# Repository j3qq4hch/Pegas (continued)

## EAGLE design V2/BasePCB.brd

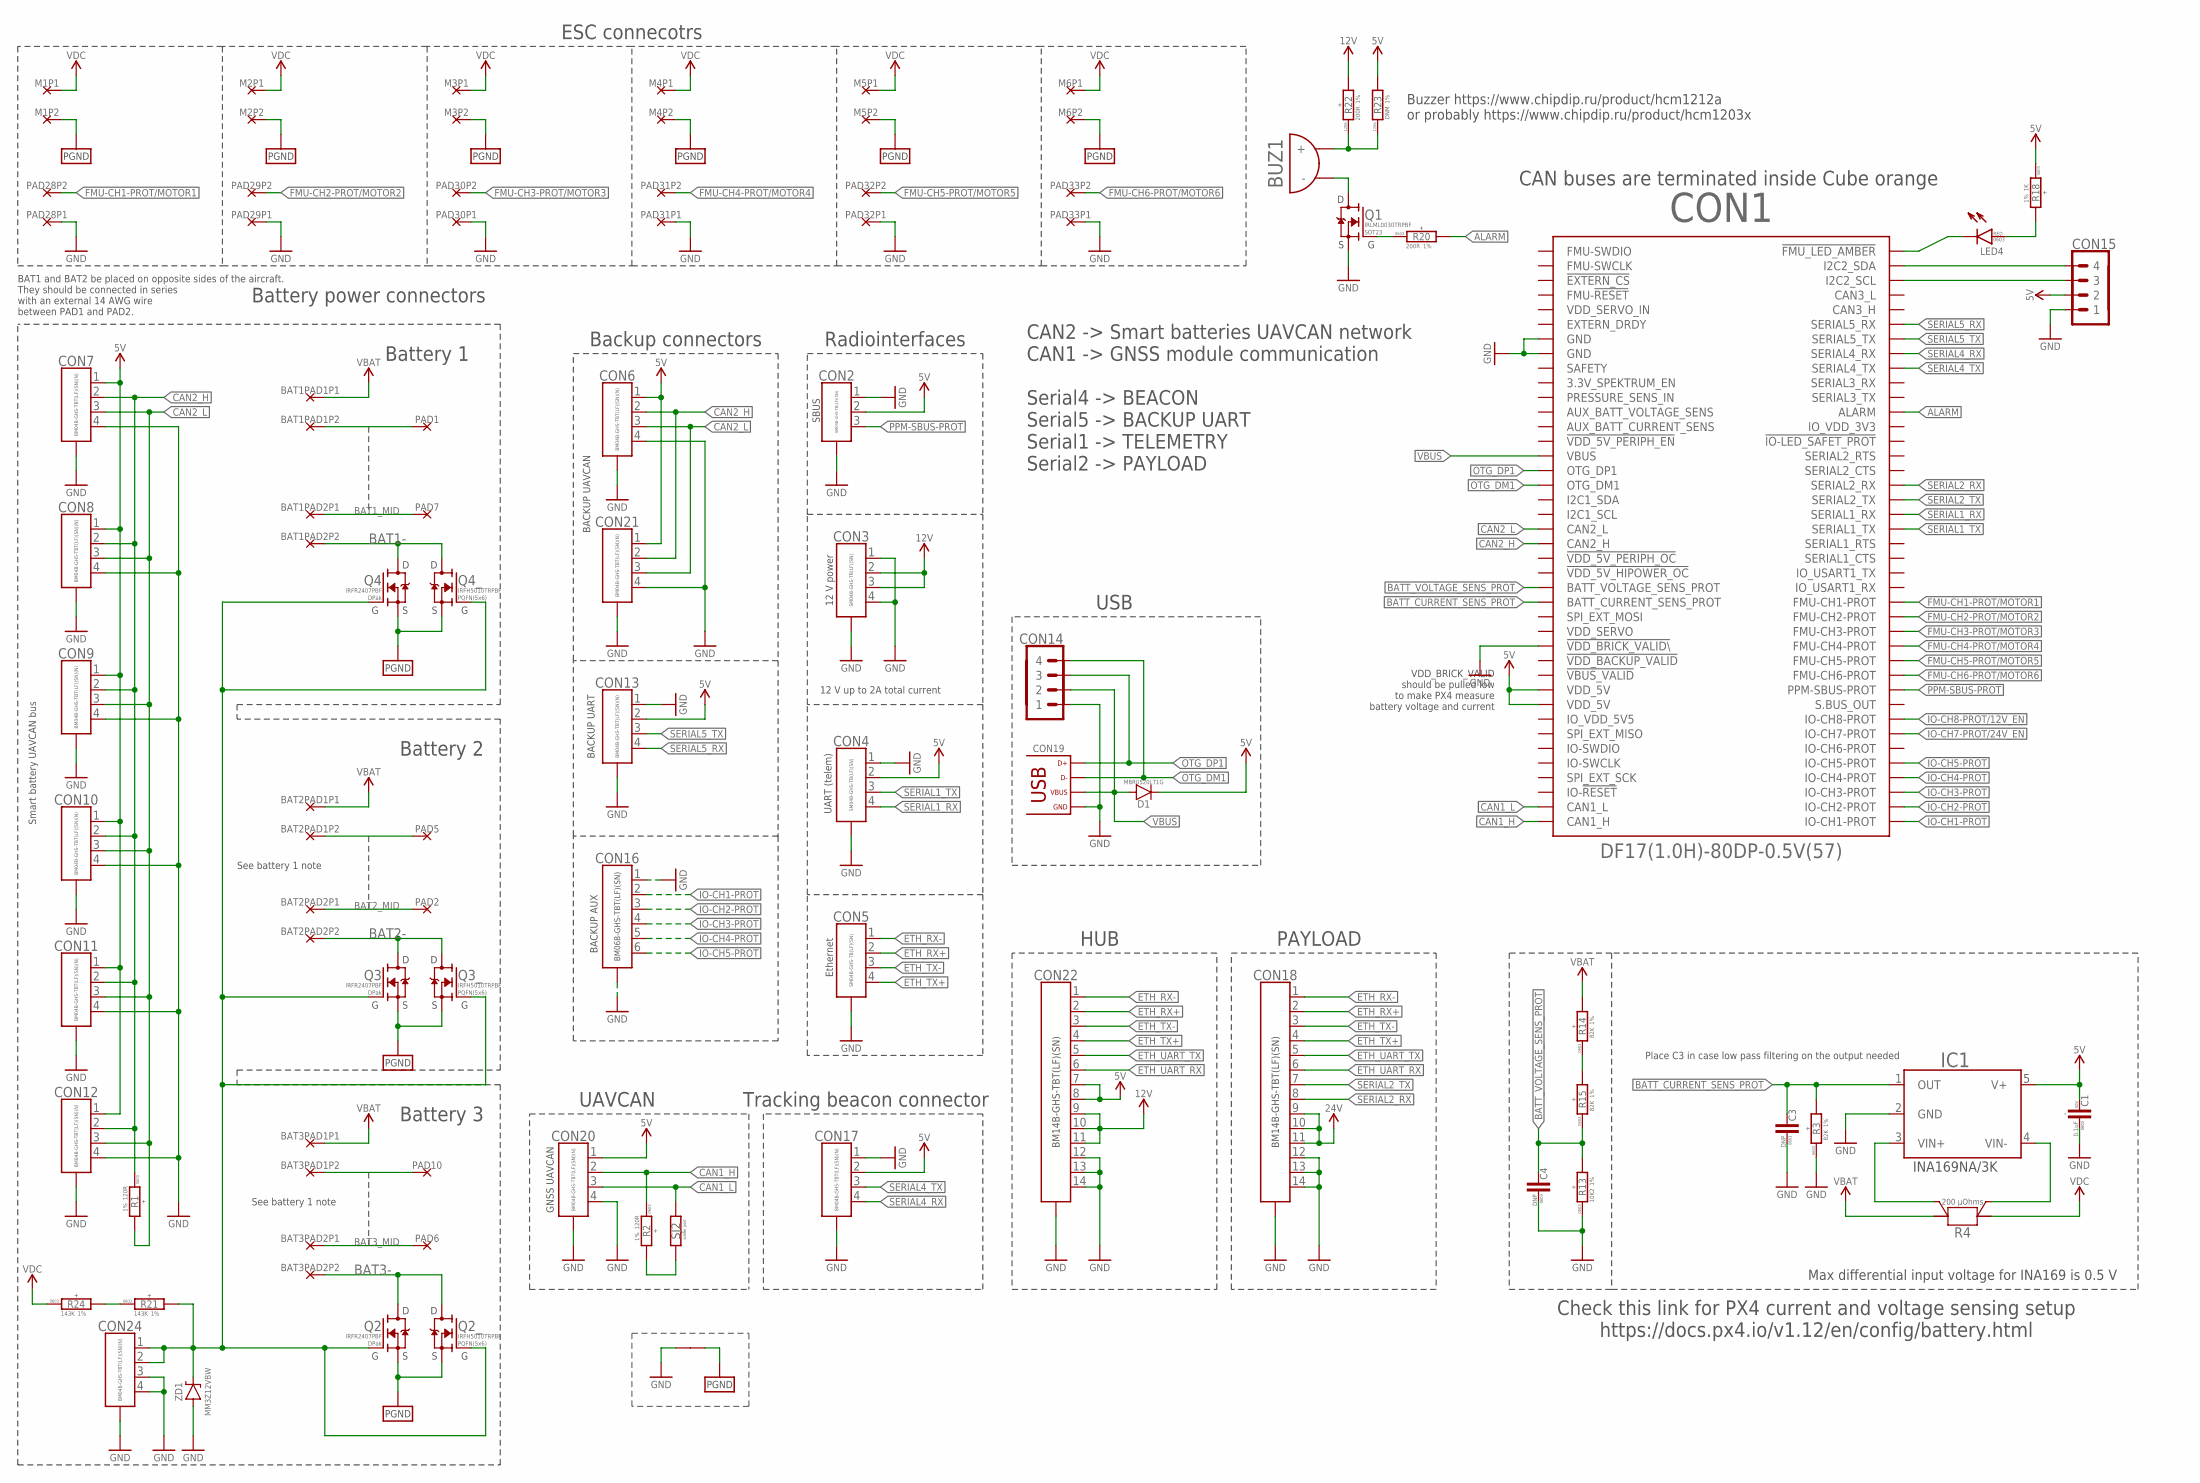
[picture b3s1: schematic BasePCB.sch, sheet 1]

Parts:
BAT1PAD1, BAT1PAD2, BAT2PAD1, BAT2PAD2, BAT3PAD1, BAT3PAD2: PAD_PAIR-4X10; 4X10_PAIR
BUZ1: BUZZER-ЕР-12MM; BUZZER_12MM
C1: 0.1uF; C0603; VOLTAGE 50V; LCSC# C14663
C3, C4: DNP; C0603
CON1: CUBE_ORANGE_; CUBE_ORANGE
CON2: CON-3P-TABS-JST-GH-SIDE; SM03B-GHS-TB
CON3, CON4, CON5: CON-4P-TABS-JST-GH-SIDE; SM04B-GHS-TB
CON6, CON7, CON8, CON9, CON10, CON11, CON12, CON13, CON17, CON20, CON21, CON24: CON-4P-TABS-JST-GH-TOP; BM04B-GHS-TB
CON14, CON15: PINHEAD_1X04-2.54; 1X04-PTH-2.54
CON16: CON-6P-TABS-JST-GH-TOP; BM06B-GHS-TBT
CON18, CON22: CON-14P-TABS-JST-GH-TOP; BM14B-GHS-TBT
CON19: USB-TYPE-C-VERT-PROD; 2047110001-PROD; LCSC# C381139
D1: MBR0520L-SOD123; SOD123
IC1: INA169; SOT23-5
J1: CONNECTION-SMD-BIG; CONNECTION_BIG
LED4: LED-0603; LED0603; LCSC# C2286
M1, M2, M3, M4, M5, M6: PAD_PAIR-4X10; 4X10_PAIR
PAD1, PAD2, PAD5, PAD6, PAD7, PAD10: PAD-10X4; 10X4
PAD28, PAD29, PAD30, PAD31, PAD32, PAD33: PAD_PAIR-2X6; 2X6_PAIR
Q1: IRLML0030; SOT23
Q2, Q3, Q4: IRFR2407PBF; D-PAK
Q2_, Q3_, Q4_: IRFH5010TRPBF-DFN5X6; PG-TDSON-8
R1, R2: 120R; R0603; LCSC# C22787
R3, R14, R15: 82K; R0603; LCSC# C23254
R4: 200 µOhms; R3920-KELVIN
R13: 10K2; R0603; LCSC# C22772
R18: 1K; R0603; LCSC# C21190
R20: 200R; R0603; LCSC# C21190
R21, R24: 143K; R0603; LCSC# C22877
R22: 200R; R1206; LCSC# C25361
R23: DNM; R1206
SJ2: SOLDER_JOINT-SJ1; RES_0
ZD1: MM3Z12VBW; SOD323

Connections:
!FMU_LED_AMBER: CON1.2 (!FMU_LED_AMBER), LED4.C
ALARM: CON1.24 (ALARM), R20.2
BAT1-: BAT1PAD2.2, Q4.D, Q4_.5D (D), Q4_.6D (D), Q4_.7D (D), Q4_.8D (D), Q4_.PAD_D (D)
BAT1_MID: BAT1PAD2.1, PAD7.P$1
BAT2-: BAT2PAD2.2, Q3.D, Q3_.5D (D), Q3_.6D (D), Q3_.7D (D), Q3_.8D (D), Q3_.PAD_D (D)
BAT2_MID: BAT2PAD2.1, PAD2.P$1
BAT3-: BAT3PAD2.2, Q2.D, Q2_.5D (D), Q2_.6D (D), Q2_.7D (D), Q2_.8D (D), Q2_.PAD_D (D)
BAT3_MID: BAT3PAD2.1, PAD6.P$1
BATT_CURRENT_SENS_PROT: C3.2, CON1.49 (BATT_CURRENT_SENS_PROT), IC1.1 (OUT), R3.2
BATT_VOLTAGE_SENS_PROT: C4.2, CON1.47 (BATT_VOLTAGE_SENS_PROT), R13.2, R15.1
CAN1_H: CON1.79 (CAN1_H), CON20.2, R2.1
CAN1_L: CON1.77 (CAN1_L), CON20.3, SJ2.2
CAN2_H: CON1.41 (CAN2_H), CON6.2, CON7.2, CON8.2, CON9.2, CON10.2, CON11.2, CON12.2, CON21.2, R1.1
CAN2_L: CON1.39 (CAN2_L), CON6.3, CON7.3, CON8.3, CON9.3, CON10.3, CON11.3, CON12.3, CON21.3, R1.2
ETH_RX+: CON5.2, CON18.2, CON22.2
ETH_RX-: CON5.1, CON18.1, CON22.1
ETH_TX+: CON5.4, CON18.4, CON22.4
ETH_TX-: CON5.3, CON18.3, CON22.3
ETH_UART_RX: CON18.6, CON22.6
ETH_UART_TX: CON18.5, CON22.5
FMU-CH1-PROT/MOTOR1: CON1.50 (FMU-CH1-PROT), PAD28.2
FMU-CH2-PROT/MOTOR2: CON1.52 (FMU-CH2-PROT), PAD29.2
FMU-CH3-PROT/MOTOR3: CON1.54 (FMU-CH3-PROT), PAD30.2
FMU-CH4-PROT/MOTOR4: CON1.56 (FMU-CH4-PROT), PAD31.2
FMU-CH5-PROT/MOTOR5: CON1.58 (FMU-CH5-PROT), PAD32.2
FMU-CH6-PROT/MOTOR6: CON1.60 (FMU-CH6-PROT), PAD33.2
GND: C1.1, C3.1, C4.1, CON1.13 (GND), CON1.15 (GND), CON1.55 (!VDD_BRICK_VALID\), CON2.1, CON2.M$0 (GND), CON2.M$1 (GND), CON3.1, CON3.4, CON3.M$0 (GND), CON3.M$1 (GND), CON4.1, CON4.M$0 (GND), CON4.M$1 (GND), CON5.M$0 (GND), CON5.M$1 (GND), CON6.4, CON6.M$0 (GND), CON6.M$1 (GND), CON7.4, CON7.M$0 (GND), CON7.M$1 (GND), CON8.4, CON8.M$0 (GND), CON8.M$1 (GND), CON9.4, CON9.M$0 (GND), CON9.M$1 (GND), CON10.4, CON10.M$0 (GND), CON10.M$1 (GND), CON11.4, CON11.M$0 (GND), CON11.M$1 (GND), CON12.4, CON12.M$0 (GND), CON12.M$1 (GND), CON13.1, CON13.M$0 (GND), CON13.M$1 (GND), CON14.1, CON15.1, CON16.1, CON16.M$0 (G1), CON16.M$1 (G1), CON17.1, CON17.M$0 (GND), CON17.M$1 (GND), CON18.12, CON18.13, CON18.14, CON18.M$0 (G1), CON18.M$1 (G1), CON19.A1 (GND), CON19.A12 (GND), CON19.B1 (GND), CON19.B12 (GND), CON19.G1 (GND), CON19.G2 (GND), CON19.G4 (GND), CON19.G5 (GND), CON19.G7 (GND), CON19.G8 (GND), CON19.G9 (GND), CON19.G10 (GND), CON19.P$1 (GND), CON19.P$2 (GND), CON20.4, CON20.M$0 (GND), CON20.M$1 (GND), CON21.4, CON21.M$0 (GND), CON21.M$1 (GND), CON22.12, CON22.13, CON22.14, CON22.M$0 (G1), CON22.M$1 (G1), CON24.3, CON24.4, CON24.M$0 (GND), CON24.M$1 (GND), IC1.2 (GND), J1.1, PAD28.1, PAD29.1, PAD30.1, PAD31.1, PAD32.1, PAD33.1, Q1.2 (S), R3.1, R13.1, ZD1.A; also elsewhere on the board
I2C2_SCL: CON1.6 (I2C2_SCL), CON15.3
I2C2_SDA: CON1.4 (I2C2_SDA), CON15.4
IO-CH1-PROT: CON1.80 (IO-CH1-PROT), CON16.2
IO-CH2-PROT: CON1.78 (IO-CH2-PROT), CON16.3
IO-CH3-PROT: CON1.76 (IO-CH3-PROT), CON16.4
IO-CH4-PROT: CON1.74 (IO-CH4-PROT), CON16.5
IO-CH5-PROT: CON1.72 (IO-CH5-PROT), CON16.6
IO-CH7-PROT/24V_EN: CON1.68 (IO-CH7-PROT); also elsewhere on the board
IO-CH8-PROT/12V_EN: CON1.66 (IO-CH8-PROT); also elsewhere on the board
unnamed: LED4.A, R18.2
unnamed: BAT1PAD1.2, PAD1.P$1
unnamed: BUZ1.2 (-), Q1.3 (D)
unnamed: BAT2PAD1.2, PAD5.P$1
unnamed: Q1.1 (G), R20.1
unnamed: BAT3PAD1.2, PAD10.P$1
unnamed: R2.2, SJ2.1
unnamed: IC1.4 (VIN-), R4.S2
unnamed: IC1.3 (VIN+), R4.S1
unnamed: R14.1, R15.2
unnamed: BUZ1.1 (+), R22.P$1 (1), R23.P$1 (1)
unnamed: R21.1, R24.2
OTG_DM1: CON1.33 (OTG_DM1), CON14.4, CON19.A7 (D-), CON19.B7 (D-)
OTG_DP1: CON1.31 (OTG_DP1), CON14.3, CON19.A6 (D+), CON19.B6 (D+)
PGND: J1.2, M1.2, M2.2, M3.2, M4.2, M5.2, M6.2, Q2.S, Q2_.1S (S), Q2_.2S (S), Q2_.3S (S), Q3.S, Q3_.1S (S), Q3_.2S (S), Q3_.3S (S), Q4.S, Q4_.1S (S), Q4_.2S (S), Q4_.3S (S)
PPM-SBUS-PROT: CON1.62 (PPM-SBUS-PROT), CON2.3
PWR_GATE: CON24.1, CON24.2, Q2.G, Q2_.4G (G), Q3.G, Q3_.4G (G), Q4.G, Q4_.4G (G), R21.2, ZD1.C
SERIAL1_RX: CON1.38 (SERIAL1_RX), CON4.4
SERIAL1_TX: CON1.40 (SERIAL1_TX), CON4.3
SERIAL2_RX: CON1.34 (SERIAL2_RX), CON18.8
SERIAL2_TX: CON1.36 (SERIAL2_TX), CON18.7
SERIAL4_RX: CON1.16 (SERIAL4_RX), CON17.4
SERIAL4_TX: CON1.18 (SERIAL4_TX), CON17.3
SERIAL5_RX: CON1.12 (SERIAL5_RX), CON13.4
SERIAL5_TX: CON1.14 (SERIAL5_TX), CON13.3
VBAT: BAT1PAD1.1, BAT2PAD1.1, BAT3PAD1.1, R4.1, R4.11 (1), R14.2
VBUS: CON1.29 (VBUS), CON14.2, CON19.A4 (VBUS), CON19.B4 (VBUS), D1.A
VDC: M1.1, M2.1, M3.1, M4.1, M5.1, M6.1, R4.2, R4.22 (2), R24.1; also elsewhere on the board
VDD_5V: C1.2, CON1.61 (VDD_5V), CON1.63 (VDD_5V), CON2.2, CON4.2, CON6.1, CON7.1, CON8.1, CON9.1, CON10.1, CON11.1, CON12.1, CON13.2, CON15.2, CON17.2, CON20.1, CON21.1, CON22.7, CON22.8, D1.C, IC1.5 (V+), R18.1, R23.P$2 (2); also elsewhere on the board
VDD_12V: CON3.2, CON3.3, CON22.9, CON22.10, CON22.11, R22.P$2 (2); also elsewhere on the board
VDD_24V: CON18.9, CON18.10, CON18.11; also elsewhere on the board

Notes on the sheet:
SBUS
12 V up to 2A total current
12 V power
UART (telem)
Ethernet
Radiointerfaces
GNSS UAVCAN
Smart battery UAVCAN bus
UAVCAN
BACKUP UAVCAN
Backup connectors
BACKUP UART
BACKUP AUX
Tracking beacon connector
Battery power connectors
ESC connecotrs
BAT1 and BAT2 be placed on opposite sides of the aircraft. They should be connected in series with an external 14 AWG wire between PAD1 and PAD2.
Battery 1
Battery 2
See battery 1 note
Battery 3
CAN buses are terminated inside Cube orange
CAN2 -> Smart batteries UAVCAN network CAN1 -> GNSS module communication Serial4 -> BEACON Serial5 -> BACKUP UART Serial1 -> TELEMETRY Serial2 -> PAYLOAD
Check this link for PX4 current and voltage sensing setup https://docs.px4.io/v1.12/en/config/battery.html
Max differential input voltage for INA169 is 0.5 V
Place C3 in case low pass filtering on the output needed
PAYLOAD
USB
VDD_BRICK_VALID should be pulled low to make PX4 measure battery voltage and current
HUB
Buzzer https://www.chipdip.ru/product/hcm1212a or probably https://www.chipdip.ru/product/hcm1203x

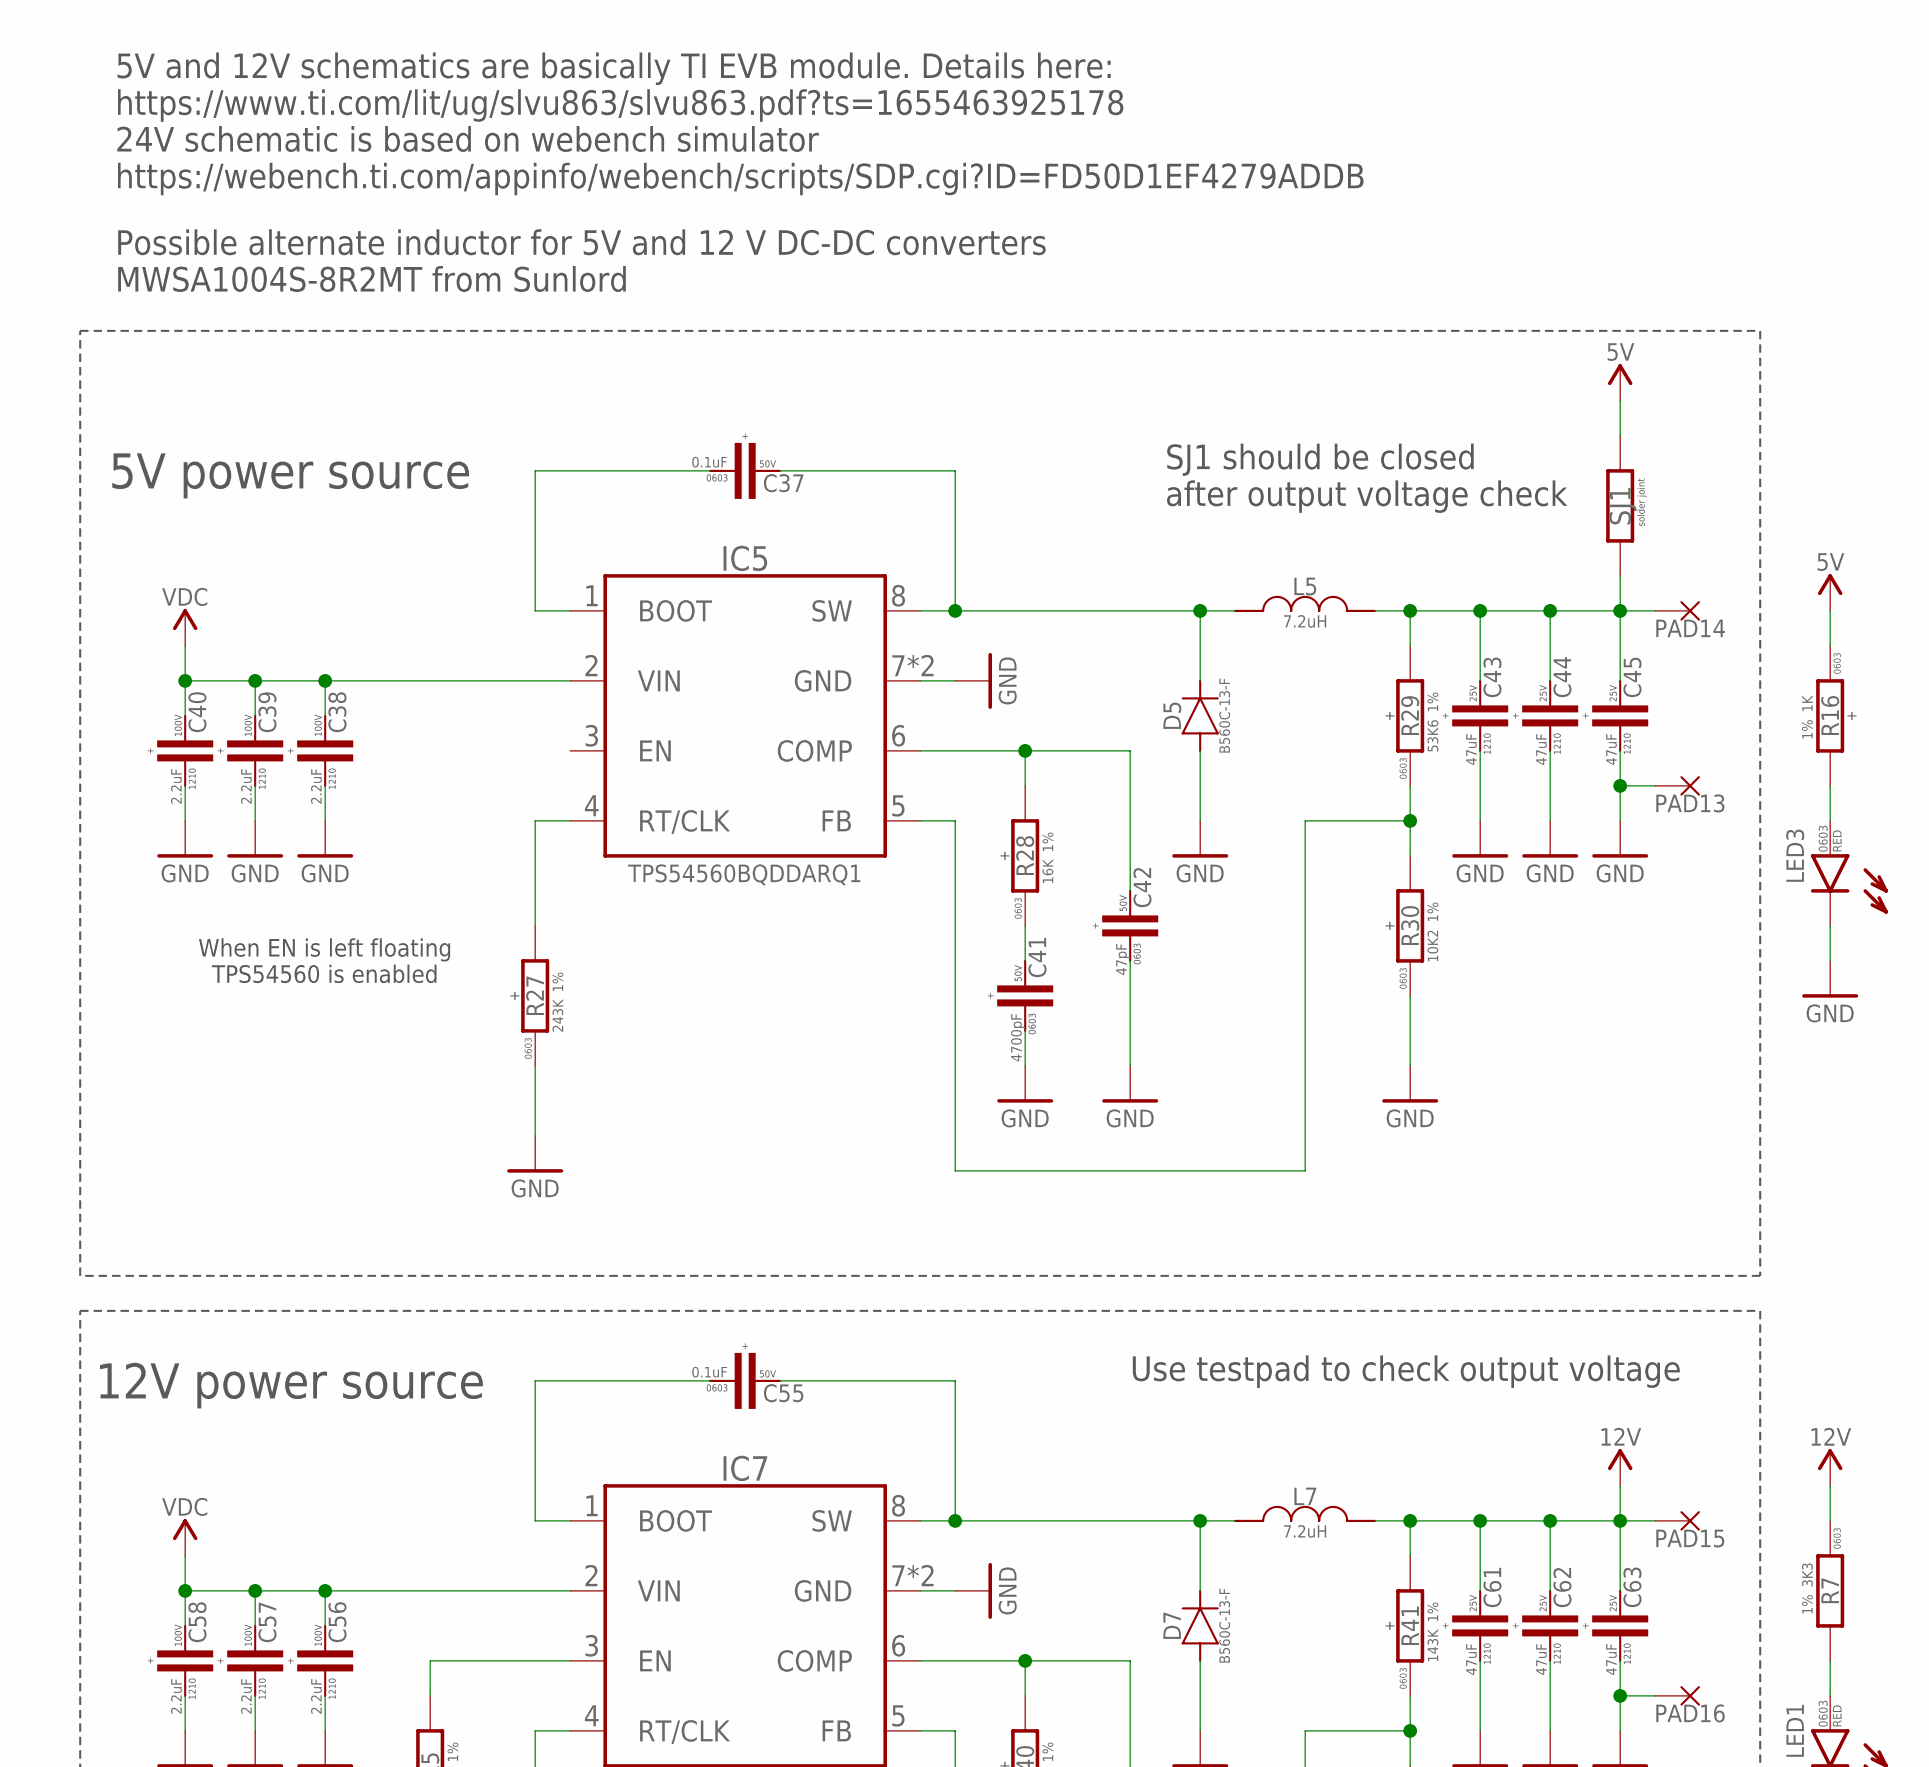
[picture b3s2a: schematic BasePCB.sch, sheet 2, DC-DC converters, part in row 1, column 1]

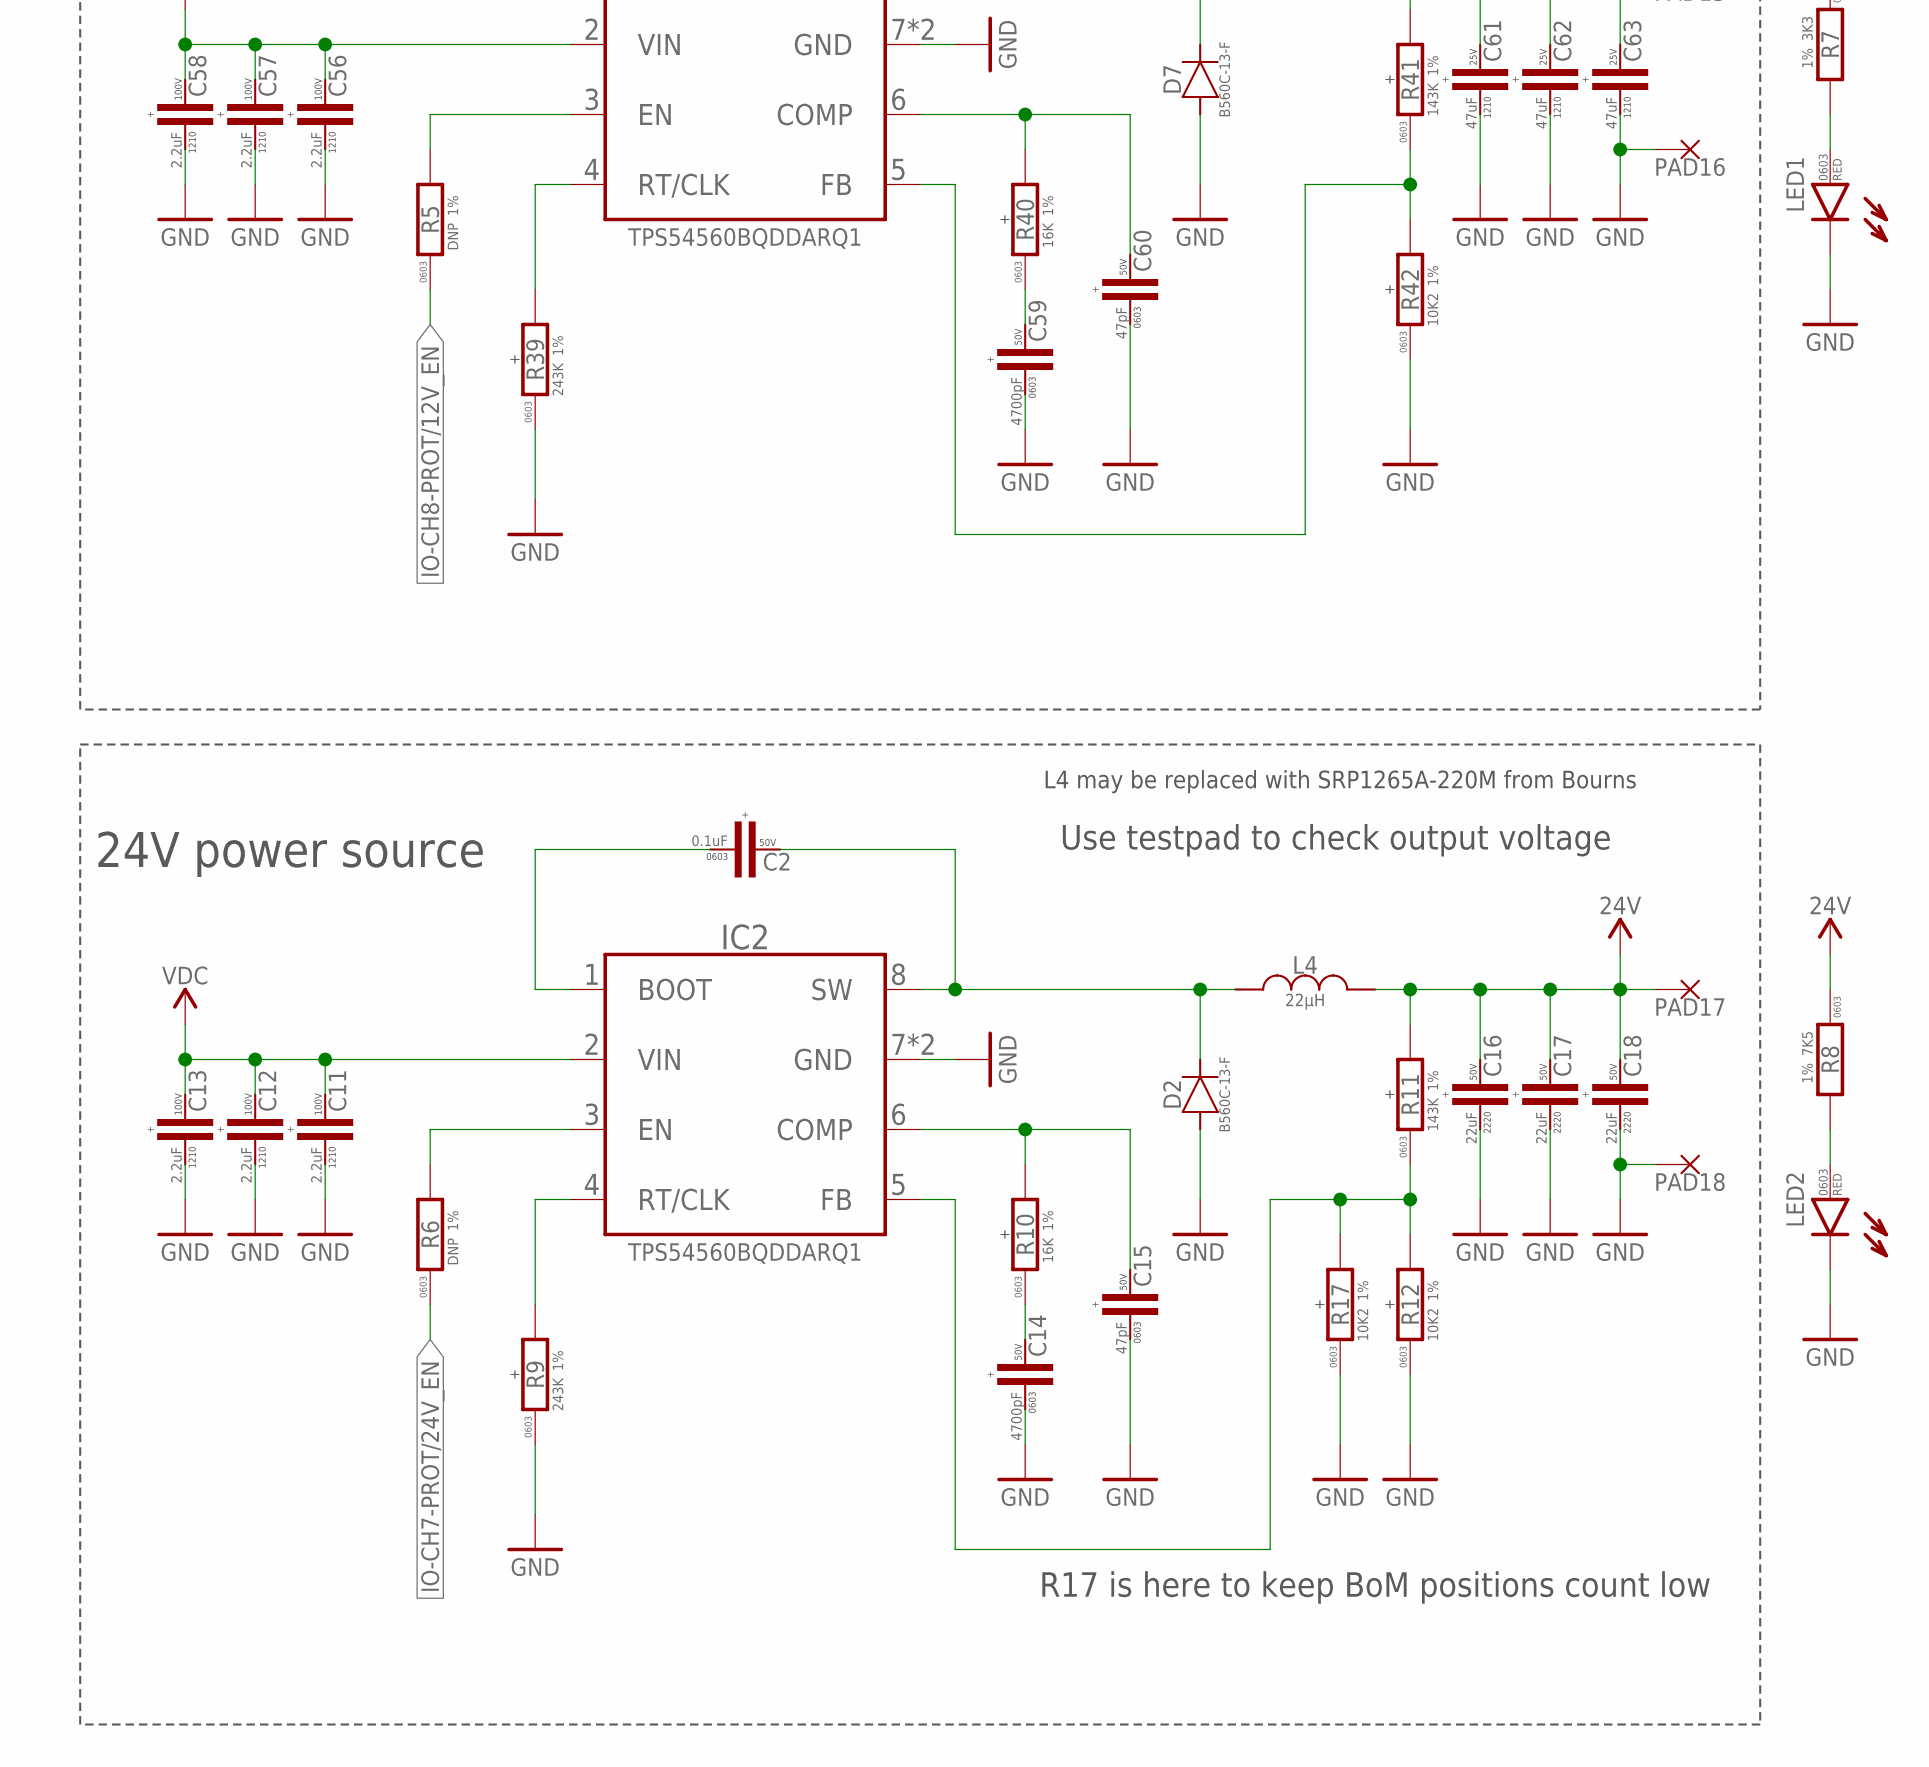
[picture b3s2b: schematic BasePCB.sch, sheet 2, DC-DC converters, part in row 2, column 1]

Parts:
C2, C37, C55: 0.1uF; C0603; VOLTAGE 50V; LCSC# C14663
C11, C12, C13, C38, C39, C40, C56, C57, C58: 2.2uF; C1210; VOLTAGE 100V; LCSC# C55151
C14, C41, C59: 4700pF; C0603; VOLTAGE 50V; LCSC# C53987
C15, C42, C60: 47pF; C0603; VOLTAGE 50V; LCSC# C1671
C16, C17, C18: 22uF; C2220; VOLTAGE 50V; LCSC# C784103
C43, C44, C45, C61, C62, C63: 47uF; C1210; VOLTAGE 25V; LCSC# C90142
D2, D5, D7: B560C; DO-214AB(SMC)
IC2, IC5, IC7: TPS54560B; SOIC8-POWERPAD
L4: 22µH; MWSA1206S
L5, L7: 7.2uH; 1064
LED1, LED2, LED3: LED-0603; LED0603; LCSC# C2286
PAD13, PAD14, PAD15, PAD16, PAD17, PAD18: PAD-S_2X2; 2х2
R5, R6: DNP; R0603
R7: 3K3; R0603; LCSC# C22978
R8: 7K5; R0603; LCSC# C23234
R9, R27, R39: 243K; R0603; LCSC# C23351
R10, R28, R40: 16K; R0603; LCSC# C4210
R11, R41: 143K; R0603; LCSC# C22877
R12, R17, R30, R42: 10K2; R0603; LCSC# C22772
R16: 1K; R0603; LCSC# C21190
R29: 53K6; R0603; LCSC# C23074
SJ1: SOLDER_JOINT-SJ1; RES_0

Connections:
GND: C11.1, C12.1, C13.1, C14.1, C15.1, C16.P$1 (1), C17.P$1 (1), C18.P$1 (1), C38.1, C39.1, C40.1, C41.1, C42.1, C43.1, C44.1, C45.1, C56.1, C57.1, C58.1, C59.1, C60.1, C61.1, C62.1, C63.1, D2.A, D5.A, D7.A, IC2.7 (GND), IC2.P$1 (GND), IC5.7 (GND), IC5.P$1 (GND), IC7.7 (GND), IC7.P$1 (GND), LED1.C, LED2.C, LED3.C, PAD13.P$1, PAD16.P$1, PAD18.P$1, R9.1, R12.1, R17.1, R27.1, R30.1, R39.1, R42.1; also elsewhere on the board
IO-CH7-PROT/24V_EN: R6.1; also elsewhere on the board
IO-CH8-PROT/12V_EN: R5.1; also elsewhere on the board
unnamed: C43.2, C44.2, C45.2, L5.2, PAD14.P$1, R29.2, SJ1.1
unnamed: IC7.3 (EN), R5.2
unnamed: C2.1, IC2.1 (BOOT)
unnamed: C2.2, D2.C, IC2.8 (SW), L4.1
unnamed: IC2.4 (RT/CLK), R9.2
unnamed: IC2.3 (EN), R6.2
unnamed: C15.2, IC2.6 (COMP), R10.2
unnamed: C14.2, R10.1
unnamed: IC2.5 (FB), R11.1, R12.2, R17.2
unnamed: LED1.A, R7.2
unnamed: LED2.A, R8.2
unnamed: LED3.A, R16.2
unnamed: C37.1, IC5.1 (BOOT)
unnamed: C37.2, D5.C, IC5.8 (SW), L5.1
unnamed: IC5.4 (RT/CLK), R27.2
unnamed: C42.2, IC5.6 (COMP), R28.2
unnamed: C41.2, R28.1
unnamed: IC5.5 (FB), R29.1, R30.2
unnamed: C55.1, IC7.1 (BOOT)
unnamed: C55.2, D7.C, IC7.8 (SW), L7.1
unnamed: IC7.4 (RT/CLK), R39.2
unnamed: C60.2, IC7.6 (COMP), R40.2
unnamed: C59.2, R40.1
unnamed: IC7.5 (FB), R41.1, R42.2
VDC: C11.2, C12.2, C13.2, C38.2, C39.2, C40.2, C56.2, C57.2, C58.2, IC2.2 (VIN), IC5.2 (VIN), IC7.2 (VIN); also elsewhere on the board
VDD_5V: R16.1, SJ1.2; also elsewhere on the board
VDD_12V: C61.2, C62.2, C63.2, L7.2, PAD15.P$1, R7.1, R41.2; also elsewhere on the board
VDD_24V: C16.P$2 (2), C17.P$2 (2), C18.P$2 (2), L4.2, PAD17.P$1, R8.1, R11.2; also elsewhere on the board

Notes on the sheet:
5V and 12V schematics are basically TI EVB module. Details here: https://www.ti.com/lit/ug/slvu863/slvu863.pdf?ts=1655463925178 24V schematic is based on webench simulator https://webench.ti.com/appinfo/webench/scripts/SDP.cgi?ID=FD50D1EF4279ADDB
Possible alternate inductor for 5V and 12 V DC-DC converters MWSA1004S-8R2MT from Sunlord
5V power source
12V power source
24V power source
SJ1 should be closed after output voltage check
Use testpad to check output voltage
When EN is left floating TPS54560 is enabled
R17 is here to keep BoM positions count low
L4 may be replaced with SRP1265A-220M from Bourns

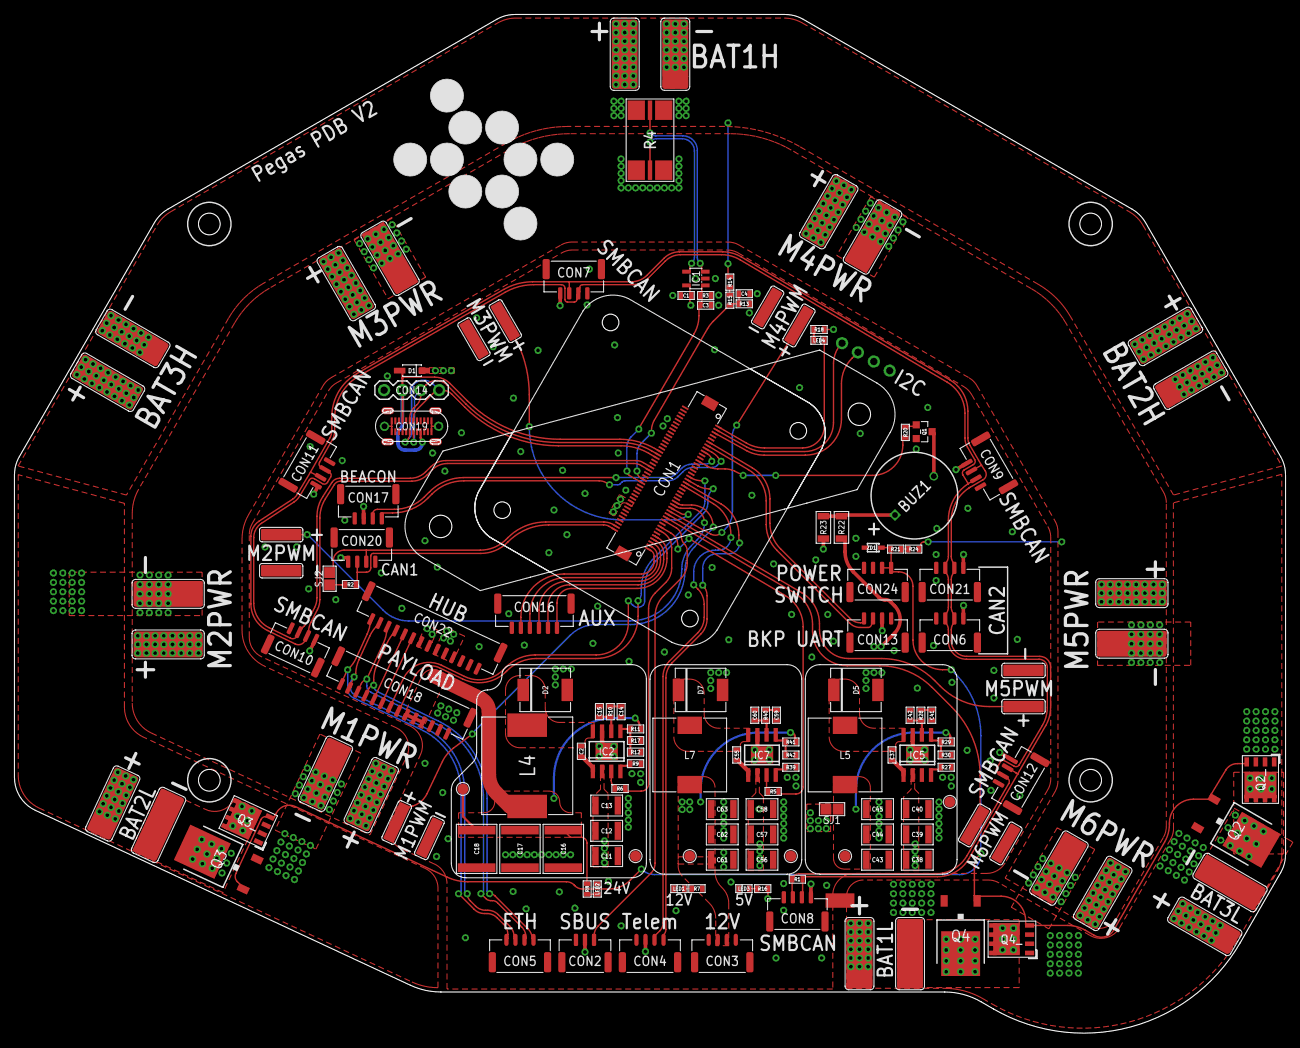
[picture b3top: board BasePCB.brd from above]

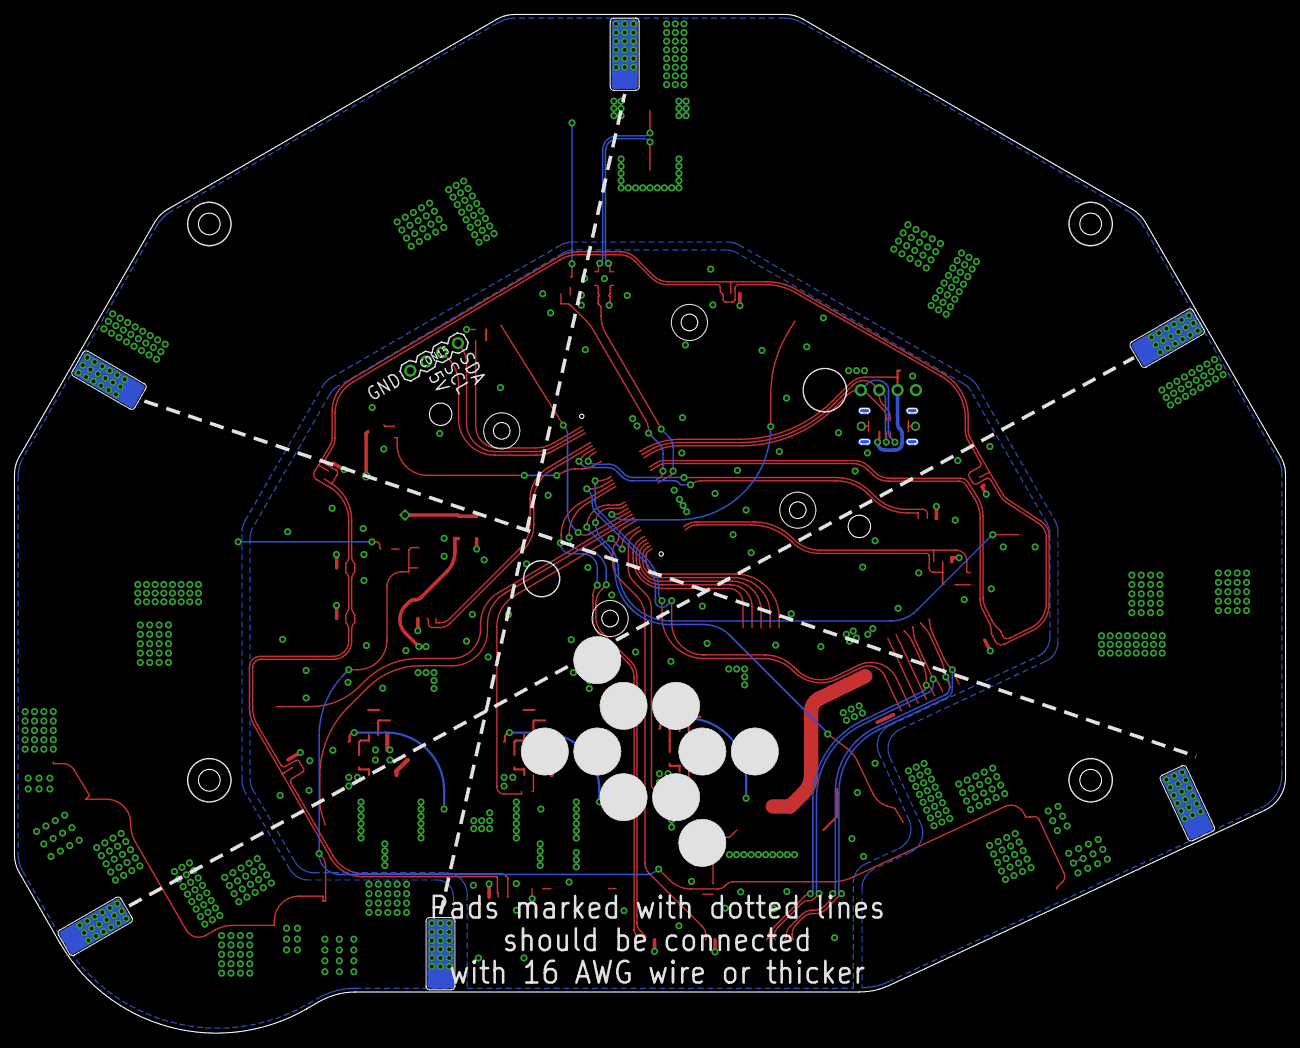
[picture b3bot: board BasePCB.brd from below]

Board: 4 copper layers, 175.9 x 141.0 mm, 144 parts (8 on the bottom side), 91 nets.

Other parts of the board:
U$1: AERODYNE
U$2: AERODYNE_SMALL
U$3: CUBE_MOUNT

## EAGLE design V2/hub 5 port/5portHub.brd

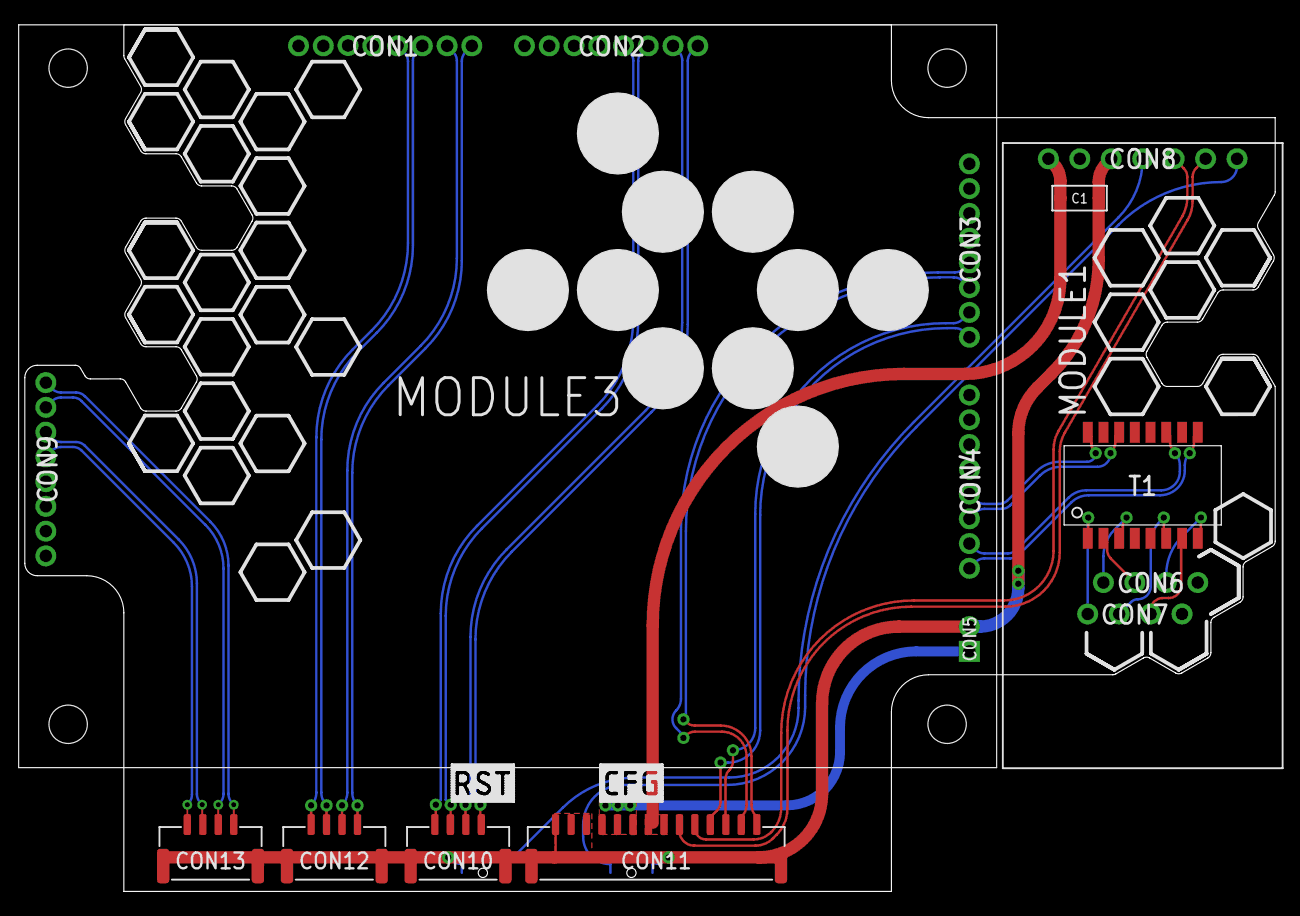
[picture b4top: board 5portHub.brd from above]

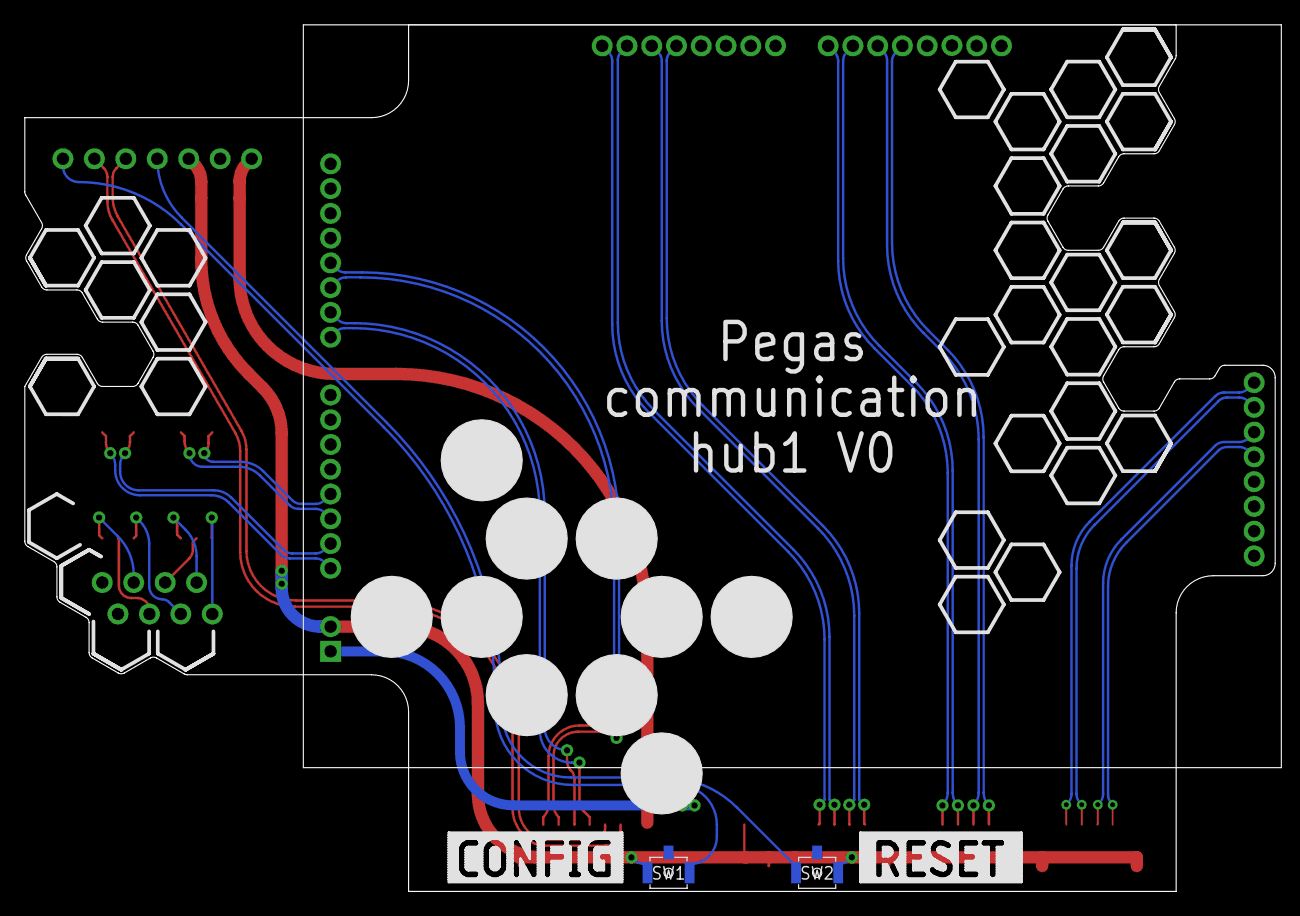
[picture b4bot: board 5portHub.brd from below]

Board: 2 copper layers, 101.0 x 70.0 mm, 12 parts (3 on the bottom side), 33 nets.

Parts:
C1: 10uF; C1206
CON10, CON12, CON13: CON-4P-TABS-JST-GH-TOP; BM04B-GHS-TB
CON11: CON-14P-TABS-JST-GH-TOP; BM14B-GHS-TBT
MODULE1: USR-TCP232-T2
MODULE3: ANDDEAR_5PORT3
SW1, SW2: TACT_SWITCH-B3U-3100P(M)-B; B3U-3100P(M)-B
T1: H1102NL; H1102
U$1, U$2: AERODYNE

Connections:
CFG: MODULE1.CFG, SW1.P$1
ETH_RX+: CON11.2, MODULE3.J3.4
ETH_RX-: CON11.1, MODULE3.J3.3
ETH_TX+: CON11.4, MODULE3.J3.1
ETH_TX-: CON11.3, MODULE3.J3.2
ETH_UART_RX: CON11.6, MODULE1.RXD
ETH_UART_TX: CON11.5, MODULE1.TXD
GND: C1.P$1, CON10.M$0, CON10.M$1, CON11.12, CON11.13, CON11.14, CON11.M$0, CON11.M$1, CON12.M$0, CON12.M$1, CON13.M$0, CON13.M$1, MODULE1.GND, MODULE3.GND, SW1.P$2, SW2.P$1
unnamed: CON13.1, MODULE3.J6.1
unnamed: CON13.2, MODULE3.J6.2
unnamed: CON13.3, MODULE3.J6.3
unnamed: CON13.4, MODULE3.J6.4
unnamed: MODULE3.J2.1, T1.9
unnamed: MODULE3.J2.2, T1.11
unnamed: MODULE3.J2.3, T1.14
unnamed: MODULE3.J2.4, T1.16
unnamed: MODULE1.J6, T1.8
unnamed: MODULE1.J1, T1.1
unnamed: MODULE1.J2, T1.3
unnamed: MODULE1.J3, T1.6
unnamed: CON12.1, MODULE3.J5.1
unnamed: CON12.2, MODULE3.J5.2
unnamed: CON12.3, MODULE3.J5.3
unnamed: CON12.4, MODULE3.J5.4
unnamed: CON10.1, MODULE3.J4.1
unnamed: CON10.2, MODULE3.J4.2
unnamed: CON10.3, MODULE3.J4.3
unnamed: CON10.4, MODULE3.J4.4
unnamed: MODULE1.J5, T1.7
unnamed: MODULE1.J4, T1.2
RST: MODULE1.RST, SW2.P$2
VDD_5V: C1.P$2, CON11.7, CON11.8, MODULE1.5V
VDD_12V: CON11.9, CON11.10, CON11.11, MODULE3.SUP
